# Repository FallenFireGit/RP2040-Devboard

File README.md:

# RP2040 Board

## NOTE TO REVIEWER

I didn’t end up recording a timelapse or keeping super consistent journal entries while working on this. Most of the project was done in longer sessions where I was focused on getting things working rather than documenting everything as I went (documenting is boring, and I got lazy). I realize now that I should’ve tracked progress better, but I’ve tried to reconstruct the main steps and decisions afterward as accurately as possible (In the 12-hour journal entry). In the future, I will remember to document more of my work as I go because I've now learned the importance of documenting. Also, this was my first project ever where I had to document, so now I understand how much I have documented moving forward. 

---

A custom-designed RP2040 development board built for expanded storage, improved power delivery, and practical usability in embedded and DIY CNC applications.

## Overview

This project is a fully custom PCB based on the RP2040 microcontroller, designed as an upgraded alternative to standard dev boards like the Raspberry Pi Pico.

The goal was to create a board that is:

* More powerful
* Easier to use during development
* Capable of handling real-world applications (data logging, robotics, etc.)

---

## Key Features

### Storage

* 8MB Flash (upgraded from 2MB)
* MicroSD Card Slot

  * Supports data logging and large file storage
  * Can be used for applications like G-code handling

---

### Interface & Controls

* Boot Button – Easy entry into bootloader mode
* Reset Button – Quick system reset during development
* Status LED (Bi-color)

  * Indicates power / charging state
* Master Power Switch

  * Fully cuts power to the board

---

### Power System

* LiPo Battery Support

  * Onboard charging circuit
* ~600mA Current Capacity

  * Supports more demanding peripherals
* 3.3V Enable Control (3V3_EN)

  * Allows software-controlled power management
* Optimized Power Traces

  * Wider 3.3V and GND lines for:

    * Reduced resistance
    * Lower heat
    * Improved stability

---

## Design Decisions

* Switched to a higher current voltage regulator for better performance
* Removed unnecessary components after redesign
* Standardized passive components to 0603:

  * Easier assembly
  * Cheaper sourcing
  * Better repairability

---

## PCB Design

* 4-Layer PCB

  * Dedicated ground plane for cleaner routing
  * Improved signal integrity and stability
* Double-sided component placement

  * Maximizes space efficiency

---

## Images

---

## Tools Used

* PCB Design: KiCad (or replace with your tool)
* Microcontroller: RP2040

---

## Status

* Schematic Complete
* PCB Layout Complete
* Manufacturing / Testing (Next Step)

---

## Goals

* Create a more capable RP2040 board than standard dev boards
* Support battery-powered applications
* Enable expandability through external storage

---

## Acknowledgments

* Inspired by the Raspberry Pi Pico
* Built as part of Hack Club Stasis

## BOM

Capacitors
* 0.1uF capacitors 402 – 10
* 1uF capacitors 402 – 2
* 10uF capacitors 805 – 5
* 22pF capacitors 402 – 2
* 0.5uF capacitor 402 – 1
* 100nF capacitor 402 – 1

Resistors
* 5.1k resistors 603 – 2
* 27.4 resistors 603 – 2 
* 100k resistors 603 – 2
* 1k resistors 603 – 3
* 10k resistors 603 – 2
* 47k resistors 603 – 3
* 200k resistor 603 – 1
* 2k resistor 603 – 1

Total Price of Passive Components ~ $1.90 (Depends on who you buy it from)

Diodes & Clock ~ $1.16
* SS14 diodes – 3 ~ $0.50 each
* SB0603W diode – 1 ~ $0.40 
* * 12MHz crystal – 1 ~ 0.70

Connectors / I/O ~ $4.75
* USB-C receptacle (HRO TYPE-C-31-M-12) – 1
* 1x20 pin headers (2.54mm) – 2
* 1x3 pin header (2.54mm) – 1
* 1x2 pin JST connector (PH series) – 1
* MicroSD card slot – 1

Switches ~ $1.20
* Push buttons (SPST) – 2
* Slider switch – 1

ICs / Chips 
* RP2040 – 1 $0.92
* MCP73831-2-OT (battery charger) – 1 $0.76
* W25Q64JVZPIQ (flash memory) – 1 $1.44
* AP2112K-3.3 (voltage regulator) – 1 $0.57

| Component | Quantity | Price (Est.) |
| :--- | :---: | :--- |
| **Passives** (Capacitors & Resistors) | 38 | $1.90 |
| **Diodes** (SS14, SB0603W) | 4 | $0.90 |
| **Clock** (12MHz Crystal) | 1 | $0.70 |
| **Connectors / I/O** (USB-C, Headers, JST, MicroSD) | 6 | $4.75 |
| **Switches** (Push buttons, Slider) | 3 | $1.20 |
| **RP2040** (Microcontroller) | 1 | $0.92 |
| **MCP73831-2-OT** (Battery Charger) | 1 | $0.76 |
| **W25Q64JVZPIQ** (Flash Memory) | 1 | $1.44 |
| **AP2112K-3.3** (Voltage Regulator) | 1 | $0.57 |
| **TOTAL** | **56** | **$13.14** |

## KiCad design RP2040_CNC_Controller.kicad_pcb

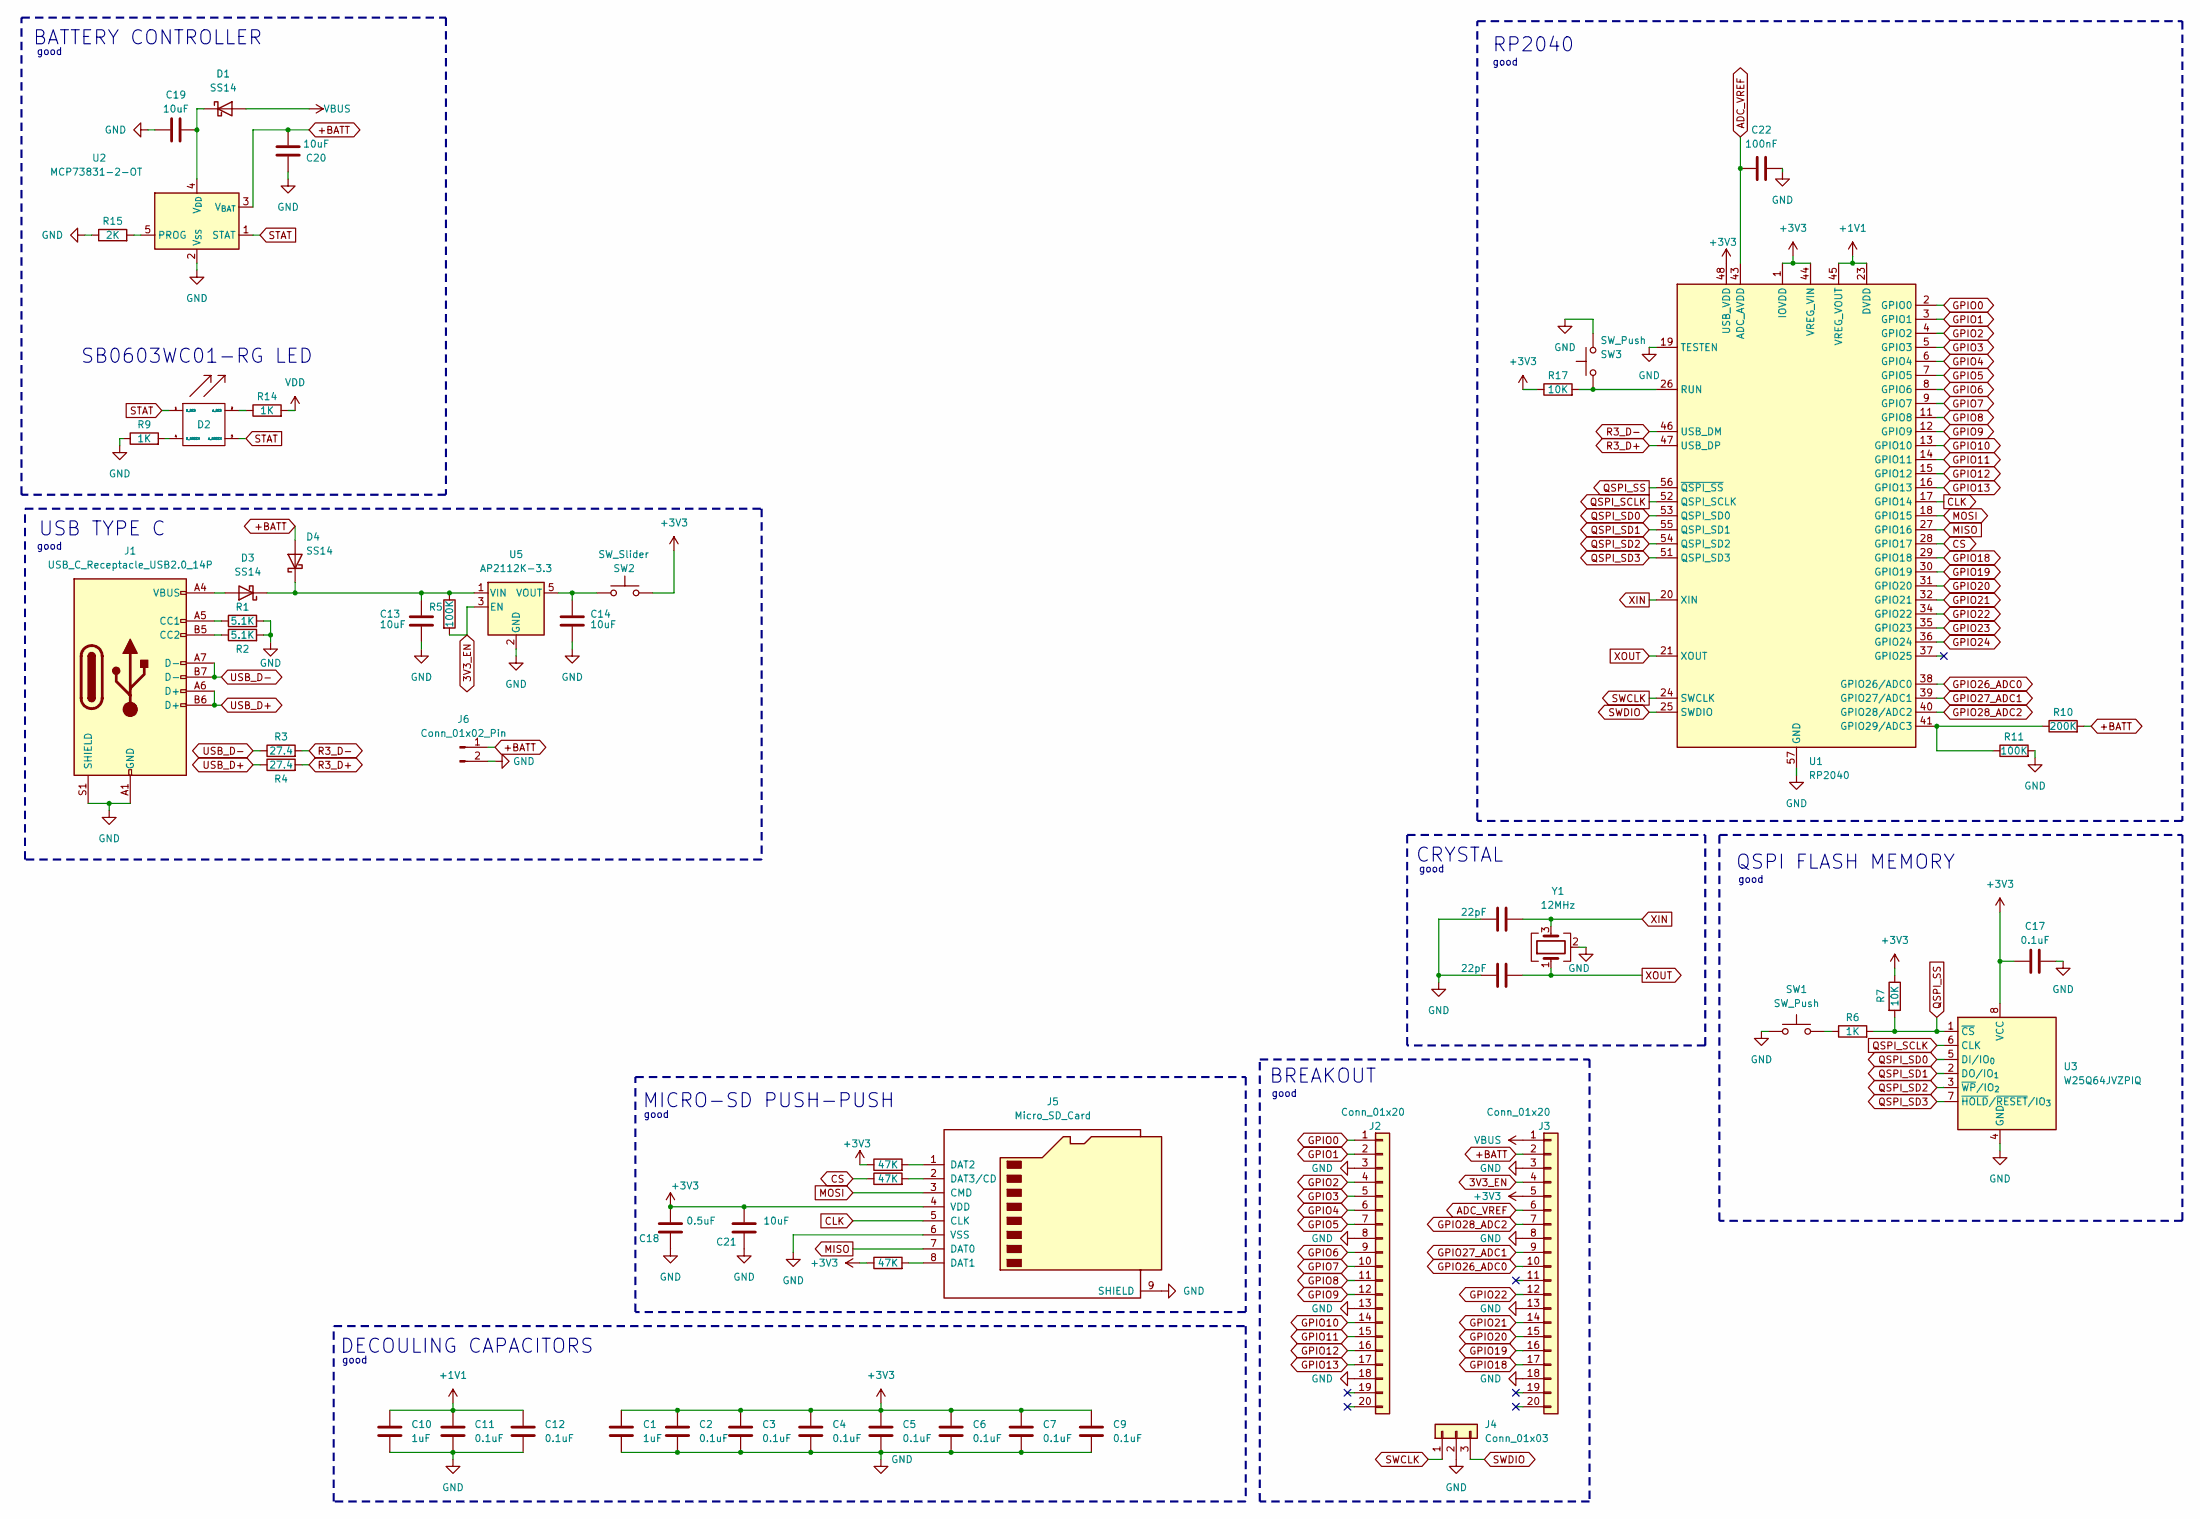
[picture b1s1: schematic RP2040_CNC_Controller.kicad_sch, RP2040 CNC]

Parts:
C1, C10: 1uF; C_0402_1005Metric
C2, C3, C4, C5, C6, C7, C9, C11, C12, C17: 0.1uF; C_0402_1005Metric
C13, C14, C19, C20, C21: 10uF; C_0805_2012Metric
C15, C16: 22pF; C_0402_1005Metric
C18: 0.5uF; C_0402_1005Metric
C22: 100nF; C_0402_1005Metric
D1, D3, D4: SS14; D_SOD-123
D2: SB0603WC01RG
J1: USB_C_Receptacle_USB2.0_14P; USB_C_Receptacle_HRO_TYPE-C-31-M-12
J2, J3: Conn_01x20; PinHeader_1x20_P2.54mm_Vertical
J4: Conn_01x03; PinHeader_1x03_P2.54mm_Vertical
J5: Micro_SD_Card; Micro_SD
J6: Conn_01x02_Pin; JST_PH_S2B-PH-K_1x02_P2.00mm_Horizontal
R1, R2: 5.1K; R_0603_1608Metric
R3, R4: 27.4; R_0402_1005Metric
R5, R11: 100K; R_0603_1608Metric
R6, R9, R14: 1K; R_0603_1608Metric
R7, R17: 10K; R_0603_1608Metric
R8, R12, R13: 47K; R_0603_1608Metric
R10: 200K; R_0603_1608Metric
R15: 2K; R_0603_1608Metric
SW1, SW3: SW_Push; SW_Push_SPST_NO_Alps_SKRK
SW2: SW_Slider; SW_DIP_SPSTx01_Slide_6.7x4.1mm_W6.73mm_P2.54mm_LowProfile_J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
U1: RP2040; QFN-56-1EP_7x7mm_P0.4mm_EP3.2x3.2mm
U2: MCP73831-2-OT; SOT-23-5
U3: W25Q64JVZPIQ; Winbond_USON-8-1EP_3x2mm_P0.5mm_EP0.2x1.6mm
U5: AP2112K-3.3; SOT-23-5
Y1: 12MHz; Crystal_SMD_3225-4Pin_3.2x2.5mm

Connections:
3V3_EN: J3.4, R5.2, U5.3 (EN)
+1V1: C10.1, C11.1, C12.1, U1.23 (DVDD), U1.45 (VREG_VOUT), U1.50 (DVDD)
+3V3: C1.1, C2.1, C3.1, C4.1, C5.1, C6.1, C7.1, C9.1, C17.1, C18.2, C21.2, J3.5, J5.4 (VDD), R7.1, R12.1, R13.1, R17.1, SW2.2, U1.1 (IOVDD), U1.10 (IOVDD), U1.22 (IOVDD), U1.33 (IOVDD), U1.42 (IOVDD), U1.44 (VREG_VIN), U1.48 (USB_VDD), U1.49 (IOVDD), U3.8 (VCC); also elsewhere on the board
+BATT: C20.1, D4.2 (A), J3.2, J6.1, R10.2, U2.3 (V_{BAT})
ADC_VREF: C22.1, J3.6, U1.43 (ADC_AVDD)
CLK: J5.5 (CLK), U1.17 (GPIO14)
CS: R8.1, U1.28 (GPIO17)
GND: C1.2, C2.2, C3.2, C4.2, C5.2, C6.2, C7.2, C9.2, C10.2, C11.2, C12.2, C13.2, C14.2, C15.1, C16.1, C17.2, C18.1, C19.1, C20.2, C21.1, C22.2, J1.A1 (GND), J1.A12 (GND), J1.B1 (GND), J1.B12 (GND), J1.S1 (SHIELD), J2.3, J2.8, J2.13, J2.18, J3.3, J3.8, J3.13, J3.18, J4.2, J5.6 (VSS), J5.9 (SHIELD), J6.2, R1.2, R2.2, R9.1, R11.2, R15.1, SW1.1, SW3.2, U1.19 (TESTEN), U1.57 (GND), U2.2 (V_{SS}), U3.4 (GND), U5.2 (GND), Y1.2 (G), Y1.4 (G); also elsewhere on the board
GPIO0: J2.1, U1.2 (GPIO0)
GPIO1: J2.2, U1.3 (GPIO1)
GPIO2: J2.4, U1.4 (GPIO2)
GPIO3: J2.5, U1.5 (GPIO3)
GPIO4: J2.6, U1.6 (GPIO4)
GPIO5: J2.7, U1.7 (GPIO5)
GPIO6: J2.9, U1.8 (GPIO6)
GPIO7: J2.10, U1.9 (GPIO7)
GPIO8: J2.11, U1.11 (GPIO8)
GPIO9: J2.12, U1.12 (GPIO9)
GPIO10: J2.14, U1.13 (GPIO10)
GPIO11: J2.15, U1.14 (GPIO11)
GPIO12: J2.16, U1.15 (GPIO12)
GPIO13: J2.17, U1.16 (GPIO13)
GPIO18: J3.17, U1.29 (GPIO18)
GPIO19: J3.16, U1.30 (GPIO19)
GPIO20: J3.15, U1.31 (GPIO20)
GPIO21: J3.14, U1.32 (GPIO21)
GPIO22: J3.12, U1.34 (GPIO22)
GPIO23: U1.35 (GPIO23)
GPIO24: U1.36 (GPIO24)
GPIO26_ADC0: J3.10, U1.38 (GPIO26/ADC0)
GPIO27_ADC1: J3.9, U1.39 (GPIO27/ADC1)
GPIO28_ADC2: J3.7, U1.40 (GPIO28/ADC2)
MISO: J5.7 (DAT0), U1.27 (GPIO16)
MOSI: J5.3 (CMD), U1.18 (GPIO15)
unnamed: C19.2, D1.1 (K), U2.4 (V_{DD})
unnamed: D2.2 (A_RED), R14.1
unnamed: D2.4 (K_GREEN), R9.2
unnamed: D3.2 (A), J1.A4 (VBUS), J1.A9 (VBUS), J1.B4 (VBUS), J1.B9 (VBUS)
unnamed: C13.1, D3.1 (K), D4.1 (K), R5.1, U5.1 (VIN)
unnamed: J1.A5 (CC1), R1.1
unnamed: J1.B5 (CC2), R2.1
unnamed: J5.8 (DAT1), R13.2
unnamed: J5.1 (DAT2), R12.2
unnamed: J5.2 (DAT3/CD), R8.2
unnamed 44: R6.1, SW1.2; also elsewhere on the board
unnamed: R10.1, R11.1, U1.41 (GPIO29/ADC3)
unnamed 46: R17.2, SW3.1, U1.26 (RUN); also elsewhere on the board
unnamed: R15.2, U2.5 (PROG)
unnamed 48: C14.1, SW2.1, U5.5 (VOUT); also elsewhere on the board
QSPI_SCLK: U1.52 (QSPI_SCLK), U3.6 (CLK)
QSPI_SD0: U1.53 (QSPI_SD0), U3.5 (DI/IO_{0})
QSPI_SD1: U1.55 (QSPI_SD1), U3.2 (DO/IO_{1})
QSPI_SD2: U1.54 (QSPI_SD2), U3.3 (~WP/IO_{2})
QSPI_SD3: U1.51 (QSPI_SD3), U3.7 (~HOLD/~RESET/IO_{3})
QSPI_SS: R6.2, R7.2, U1.56 (~QSPI_SS), U3.1 (~CS)
R3_D+: R4.2, U1.47 (USB_DP)
R3_D-: R3.2, U1.46 (USB_DM)
STAT: D2.1 (K_RED), D2.3 (A_GREEN), U2.1 (STAT)
SWCLK: J4.1, U1.24 (SWCLK)
SWDIO: J4.3, U1.25 (SWDIO)
USB_D+: J1.A6 (D+), J1.B6 (D+), R4.1
USB_D-: J1.A7 (D-), J1.B7 (D-), R3.1
VBUS: D1.2 (A), J3.1
VDD: R14.2
XIN: C15.2, U1.20 (XIN), Y1.3
XOUT: C16.2, U1.21 (XOUT), Y1.1

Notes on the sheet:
good
DECOULING CAPACITORS
MICRO-SD PUSH-PUSH
BREAKOUT
BATTERY CONTROLLER
CRYSTAL
SB0603WC01-RG LED
QSPI FLASH MEMORY
USB TYPE C
RP2040

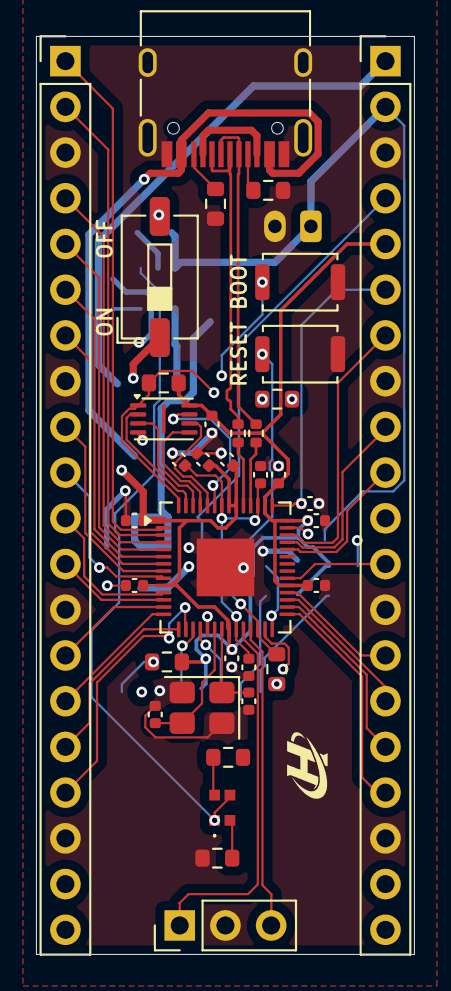
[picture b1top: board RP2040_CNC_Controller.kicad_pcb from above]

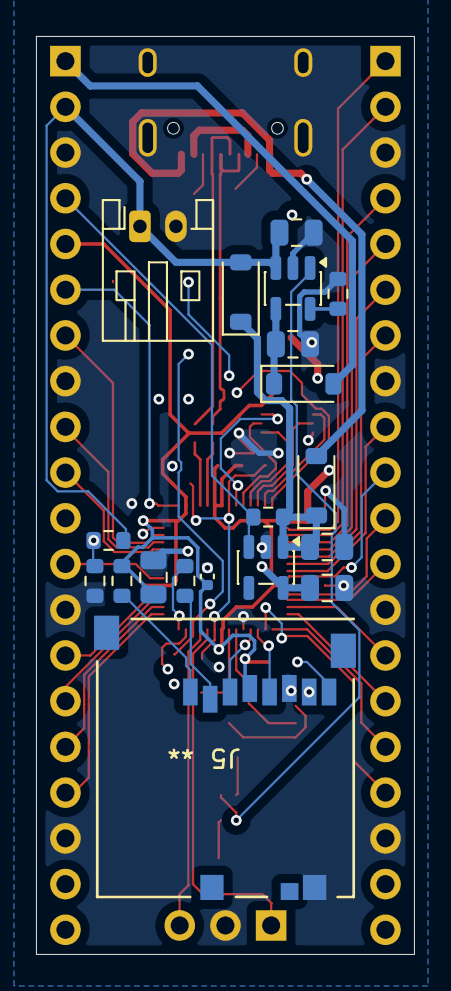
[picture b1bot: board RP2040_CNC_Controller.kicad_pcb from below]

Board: 4 copper layers, 21.0 x 51.0 mm, 55 parts (19 on the bottom side), 63 nets.

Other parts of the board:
BOOT: SW_Push; SW_Push_SPST_NO_Alps_SKRK
ON: SW_Slider; SW_DIP_SPSTx01_Slide_6.7x4.1mm_W6.73mm_P2.54mm_LowProfile_J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
RESET: SW_Push; SW_Push_SPST_NO_Alps_SKRK

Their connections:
+3V3: ON.2; also elsewhere on the board
GND: BOOT.1, RESET.2; also elsewhere on the board
unnamed 44: BOOT.2; also elsewhere on the board
unnamed 46: RESET.1; also elsewhere on the board
unnamed 48: ON.1; also elsewhere on the board

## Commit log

2026-05-03 Create asdf
2026-05-03 Rename RP2040_CNC_Controller.kicad_pcb to PCB Files/RP2040_CNC_Controller.kicad_pcb
2026-05-03 Rename RP2040_CNC_Controller.kicad_pro to PCB Files/RP2040CNC_Controller.kicad_pro
2026-05-03 Rename RP2040_CNC_Controller.kicad_sch to PCB Files/RP2040_CNC_Controller.kicad_sch
2026-05-03 Rename RP2040_Manufactuer.zip to Gerber Files/RP2040_Manufactuer.zip
